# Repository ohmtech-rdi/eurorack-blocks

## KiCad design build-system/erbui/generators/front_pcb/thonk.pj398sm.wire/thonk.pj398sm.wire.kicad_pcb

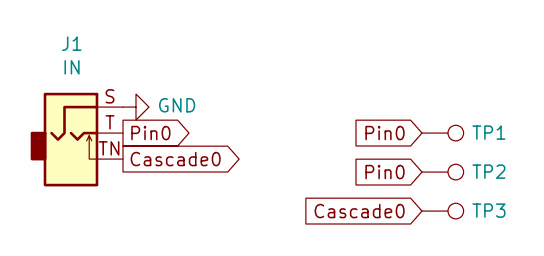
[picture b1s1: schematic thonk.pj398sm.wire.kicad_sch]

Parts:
J1: IN; ThonkiconnJack
TP1, TP2, TP3: TestPoint; TestPoint_Pad_D1.5mm

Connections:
GND: J1.S
Normalling0: J1.TN, TP3.1
Pin0: J1.T, TP1.1, TP2.1

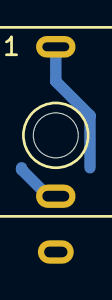
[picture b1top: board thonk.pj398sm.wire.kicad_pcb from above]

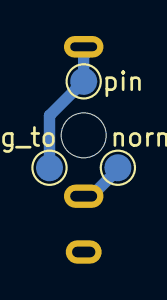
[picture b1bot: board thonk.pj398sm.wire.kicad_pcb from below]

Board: 2 copper layers, 4 parts (3 on the bottom side), 2 nets.
